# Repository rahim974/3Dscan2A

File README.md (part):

# 3Dscan2A : prototype A (carte fille sur STM32N6570-DK)

Scanner 3D portable, projet ENSEA 2A. Cette branche (`prototype_A`) porte le **prototype A** : une carte fille enfichée sur le kit ST **STM32N6570-DK**, comme un shield Arduino. Le kit apporte le calcul (STM32N6 avec NPU), la caméra IMX335 et l'écran. La carte fille apporte les capteurs et le sans-fil.

Le prototype C (carte autonome STM32H7S3, LQFP-144) viendra ensuite et réutilisera les blocs lidar, IMU et Wi-Fi validés ici.

```
            ┌──────────────────────── Carte fille (ce PCB) ────────────────────────┐
            │  VL53L9CX ◄─ I3C 1,8 V ─ TCA39306 ─ I3C 3,3 V ┐                      │
            │  LSM6DSV16X ◄──────────── I²C 3,3 V ──────────┤                      │
            │  ST67W611M1 ◄──────────── SPI 3,3 V ──────────┤   connecteurs        │
            │  LDO 3V3 / 1V8 / 1V2, oscillateur 24 MHz      ├── Arduino            │
            └───────────────────────────────────────────────┼──────────────────────┘
                                                            ▼
                      STM32N6570-DK : STM32N6 + NPU, caméra IMX335, écran, USB
                                                            │ Wi-Fi 6 / USB
                                                            ▼
                                                 PC : reconstruction 3D
```

**Répartition du traitement** (décidée le 03/11/2026) :

- **Sur le kit** : l'IA tourne sur le NPU et détecte ou segmente les objets sur l'image caméra. Elle fusionne le résultat avec la profondeur du lidar et l'orientation de l'IMU. L'**écran du kit** affiche en direct l'image, la profondeur et les objets détectés : c'est le retour visuel pendant le scan.
- **Sur le PC** : il reçoit les données déjà traitées par **Wi-Fi** (profondeur + étiquettes + orientation, horodatées) et assemble le **modèle 3D complet de la pièce** (recalage des nuages de points, maillage). Le N6 n'a ni la mémoire ni la puissance pour cette étape.
- L'USB du kit reste une solution de repli filaire pour envoyer les mêmes données.

---

## 1. Le PCB KiCad à concevoir

Une carte 2 couches au format shield Arduino Uno R3, sans microcontrôleur, sans BGA et sans mémoire externe. Elle s'enfiche sur les 4 barrettes Arduino du kit (CN8, CN7, CN11, CN12).

**État (08/11/2026)** : le projet KiCad est dans [`carte_fille_A/`](carte_fille_A/). Il part du schéma du prototype 1 (mêmes symboles et empreintes pour le lidar, l'IMU et le Wi-Fi). Le 08/11/2026, tous les composants actifs et connecteurs ont été revus avec leurs datasheets ; les corrections sont listées dans « Points à vérifier » ci-dessous.

- **Schéma** : 6 feuilles, ERC sans erreur. Un seul avertissement, exclu volontairement : la bille E5 (VSS) du lidar passe par R14 avant la masse.
- **PCB** : contour Uno R3 (68,6 × 53,3 mm), les 4 barrettes en place côté B, empreintes pré-placées par bloc, plan de masse sur B.Cu. Mis à jour depuis le schéma le 08/11/2026 (TCA39306 en VSSOP-8, R11 à R14, C36, J5 en 1×5) : placer les nouvelles empreintes. **Pas encore routé.**
- Le schéma et le placement sont générés par `carte_fille_A/generateur/design_A.py` puis `pcb_A.py` (Python de KiCad). Une fois qu'on retouche à la main dans KiCad, on ne relance plus les scripts.

| Feuille | Contenu |
|---|---|
| `connecteurs` | 4 barrettes Arduino mâles (CN8, CN7, CN11, CN12), point de test IOREF |
| `alimentation` | 5 V du kit → LD39150 (+3V3) → LDK130 (+1V8, +1V2), LED de présence, points de test |
| `lidar` | VL53L9CX, translateur I3C TCA39306, 3 × SN74LVC1T45 (XSHUT, SYNC_IN, INTR), oscillateur 24 MHz |
| `imu` | LSM6DSV16X sur le bus D14/D15, INT1/INT2 |
| `wifi` | ST67W611M1 sur le SPI5 (D10–D13), SPI_RDY, CHIP_EN, UART vers D0/D1 et header UART/BOOT |
| `mecanique` | 2 trous M2 pour le module caméra |

**Affectation des broches Arduino**

| Broche | Port N6 | Signal |
|---|---|---|
| D0 / D1 | PF6 / PD5 | UART du module Wi-Fi (par 0 Ω) |
| D2 | PD0 | Wi-Fi SPI_RDY (EXTI) |
| D3 | PE9 | SYNC_IN du lidar (sortie timer, TIM1_CH1 à confirmer) |
| D4 | PH5 | INTR du lidar (EXTI) |
| D5 | PE10 | INT1 de l'IMU (EXTI 10) |
| D7 | PD6 | CHIP_EN du Wi-Fi |
| D8 | PE7 | XSHUT du lidar |
| D9 | PE14 | INT2 de l'IMU (EXTI 14). Pas D6/PE13 : l'EXTI 13 sert au bouton USER1 du kit (PC13). |
| D10–D13 | PA3, PG2, PH8, PE15 | SPI5 vers le Wi-Fi (NSS, MOSI, MISO, SCK) |
| D14 / D15 | PC1 / PH9 | Bus I3C du lidar et de l'IMU (I3C vérifié dans CubeMX le 03/11/2026) |
| CN8 5V / GND | | Alimentation de la carte |

**Points à vérifier avant le routage**

- ~~**I3C sur D14/D15**~~ : vérifié dans CubeMX. Reste à voir **quels composants du kit sont déjà sur I2C1 (PH9/PC1)** : un composant I²C sans filtre anti-parasites de 50 ns peut perturber l'I3C. Les options de repli (I3C sur A4/A5, pull-ups I²C) ont été retirées de la carte le 03/11/2026 : en cas de problème, il faudra une nouvelle version du PCB.
- **Timer sur PE9** (D3) pour SYNC_IN : vérifier dans CubeMX qu'une sortie timer y est disponible (TIM1_CH1 ?).
- **EXTI** : D2 = ligne 0, D4 = ligne 5, D5 = ligne 10, D9 = ligne 14. Ne pas activer en interruption le TOF_INT de la caméra (PQ0, ligne 0), qui est en conflit avec D2.
- **Translateur I3C** : le NXP P3A9606 prévu au départ est limité à 1,98 V des deux côtés, donc incompatible avec le 3,3 V du kit. Il est remplacé par le **TI TCA39306DCUR** (VSSOP-8), câblé selon la figure 9-7 du datasheet : 200 kΩ + 100 pF sur VREF2/EN, pull-ups 2,2 kΩ côté 1,8 V (et non 1 kΩ : le lidar ne garantit son niveau bas qu'à faible courant, et le kit ajoute déjà 1,5 kΩ côté 3,3 V). C'est un FET passif : démarrer l'I3C en push-pull vers 5 MHz et monter en vérifiant les fronts (ST annonce 30 images/s en 54 × 42 sur I3C).
- **Revue datasheets du 08/11/2026** (autres corrections) :
  - Condensateur de découplage de l'oscillateur Y1 (C12) déplacé du +3V3 au **+1V8**, la tension d'alimentation de Y1.
  - Bille **E5** du lidar reliée à la masse par **R14 (0 Ω)** : VSS dans la datasheet rev 9, mais nommée VPP sur les cartes d'évaluation ST. On retire R14 si ST confirme que c'est VPP.
  - **J5** passe en 1×5 (GND, TX, RX, BOOT, +3V3) : un cavalier entre les broches 4 et 5 met BOOT à 1 pour la mise à jour du module Wi-Fi.
  - **LDO 3,3 V** : le rail peut tirer environ 1 A en pointe (lidar + Wi-Fi). On garde le LD39150 avec une grande zone de cuivre et des vias sous sa languette ; on passera à un régulateur à découpage si la consommation moyenne mesurée dépasse environ 0,6 A.
- **Sens de la carte** : en vue de dessus, CN8/CN7 sont en bas et D15…D0 en haut, comme une Uno vue de dessus et comme sur la photo du dessous du kit. L'empreinte KiCad `Module:Arduino_UNO_R3` met l'alimentation en haut, ce qui donnerait une carte en miroir : je ne l'ai pas utilisée. À contrôler en posant un tirage papier 1:1 sur le kit.
- ~~**Antenne Wi-Fi**~~ : au bord côté CN7, tournée vers l'extérieur, avec une zone sans cuivre sur toutes les couches (12,3 × 4,9 mm, DS14784 §6.2). ST conseille de mettre le module dans un coin de la carte, ce qui n'est pas possible ici à cause des barrettes. On le garde au milieu du bord.
- ~~**Empreintes ST**~~ (vérifiées le 03/11/2026, elles viennent d'Ultra Librarian et SnapEDA, pas de ST) :
  - VL53L9CX : 42 pastilles conformes au « solder pattern » du datasheet (DS14879, figure 30).
  - ST67W611M1 : 36 pastilles conformes à la figure 8 de DS14784, brochage conforme au tableau 1.
  - LSM6DSV16X : 14 pastilles qui couvrent les plots du boîtier (DS13510, figure 33), sens du boîtier correct. J'ai corrigé son courtyard, qui était mal formé.
- **Trous de la caméra** (H1, H2) au bord opposé, côté nappe, à côté du lidar : entraxe à mesurer sur le module.

**Orientation retenue (d'après les photos du kit)**

Les connecteurs Arduino (CN8 alimentation, CN7 A0–A5, D0–D15) sont **sous le kit**, sur la face opposée à l'écran. Le STMod+ (CN4) est sur la face de l'écran, au bord haut. La caméra n'est pas soudée au kit : c'est un module séparé relié par une **nappe** au bord haut.

On tient donc le scanner comme un appareil photo, écran vers l'utilisateur :

```
   utilisateur  →  [ écran ]  kit MB1939  [ carte fille ]  →  lidar + caméra  →  scène
                                  (Arduino dessous)
```

- La carte fille s'enfiche **sous le kit**, et le lidar est sur sa face extérieure. Il regarde la scène, à l'opposé de l'écran : c'est le bon sens.
- Le **module caméra est fixé sur la carte fille**, à côté du lidar, avec des entretoises. La nappe fait le tour du bord haut du kit. Le lidar et la caméra sont alors rigidement liés et regardent dans la même direction, ce qui simplifie l'étalonnage.
- Le **STMod+ n'est pas utilisé** : il est sur l'autre face du kit, il faudrait une nappe pour le rejoindre, et il n'apporte rien que l'Arduino n'ait déjà (son SPI5 est le même que sur D10–D13, son UART le même que sur D0/D1). On ne le garde qu'en **repli** : si l'I3C du N6 ne sort pas sur l'Arduino mais sur une broche du STMod+, on le relie par un petit câble plat.

**Contraintes de placement**

- Le lidar doit regarder **dans la même direction que la caméra**. Avec l'orientation ci-dessus, la carte fille doit prévoir les trous de fixation du module caméra à côté du lidar.
- La carte fille doit éviter les composants hauts du dessous du kit : prise Ethernet, USB-A, jack audio, lecteur micro-SD, et laisser l'accès aux USB-C (ST-LINK et USB1). Les entretoises du kit (pieds en laiton aux coins) donnent la hauteur minimale.
- L'**antenne PCB** du module Wi-Fi doit être en bord de carte, sans cuivre ni composant dessous ni autour (voir le datasheet du module), et loin des parties métalliques du kit.
- L'IMU près du lidar, sur la même carte rigide, pour que la transformation lidar ↔ IMU reste fixe.
- Les pistes I3C courtes et sans stub, le translateur au plus près du lidar.

---

## 2. Composants nécessaires

### Actifs

| Composant | Référence | Boîtier | Utilité |
|---|---|---|---|
| Lidar 3D ToF | ST **VL53L9CX** (commande : VL53L9CXV0VE/1) | Module LGA | Carte de profondeur 54×42 zones, jusqu'à 8,8 m |
| Centrale inertielle 6 axes | ST **LSM6DSV16X** | LGA-14 | Orientation et mouvement du scanner (fusion SFLP) |
| Module Wi-Fi 6 / BLE 5.4 | ST **ST67W611M1** | Module LGA, antenne PCB | Envoi des scans au PC, commandes en BLE |
| Translateur I3C 3,3 V ↔ 1,8 V | TI **TCA39306DCUR** | VSSOP-8 | Passe l'I3C du N6 (3,3 V) au lidar (1,8 V), jusqu'à 12,5 MHz |
| Translateur GPIO 3,3 V ↔ 1,8 V | TI **SN74LVC1T45** ×3 | SOT-23-6 | XSHUT, INTR et SYNC_IN du lidar |
| Oscillateur 24 MHz 1,8 V | ECS-2520MV-240 (1,6 à 3,6 V) | 2520 | Horloge AP_CLK du lidar |
| LDO 1,8 V 300 mA | ST **LDK130-18** | SOT-23-5 | IOVDD du lidar, côté 1,8 V des translateurs, oscillateur |
| LDO 1,2 V 300 mA | ST **LDK130-12** | SOT-23-5 | DVDD du lidar |
| LDO 3,3 V 1,5 A | ST **LD39150DT33** | DPAK | 3V3 depuis le 5 V du kit pour le Wi-Fi et le lidar (pointes ≈ 1 A) |

### Passifs et connectique

| Composant | Utilité |
|---|---|
| Barrettes mâles Arduino Uno R3 : 1×10, 1×8, 1×8, 1×6, pas de 2,54 mm (hauteur à choisir selon §3) | Enfichage sur le kit |
| Header 1×5, 2,54 mm | UART + BOOT + 3,3 V du module Wi-Fi (cavalier BOOT) |
| Condensateurs 100 pF / 100 nF / 1 µF (0402), 4,7 µF / 10 µF (0603), 22 µF (0805) | Découplage du lidar, du Wi-Fi, de l'IMU et des LDO |
| Résistances 1 kΩ, 2,2 kΩ, 10 kΩ, 100 kΩ, 200 kΩ, 33 Ω, 0 Ω | Pull-ups et pull-downs (I3C, XSHUT, SYNC, INTR, CHIP_EN, BOOT), polarisation du TCA39306, série de l'horloge, liaison UART Wi-Fi ↔ D0/D1, masse de E5 |
| LED + résistance | Présence d'alimentation |

Les valeurs exactes sont dans [`carte_fille_A/Nomenclature_carte_fille_A.md`](carte_fille_A/Nomenclature_carte_fille_A.md), et les références à commander dans [`carte_fille_A/Achats_composants_specifiques.md`](carte_fille_A/Achats_composants_specifiques.md).

---

## 3. Mesures et vérifications à faire sur le kit

À faire **avant** de dessiner le contour du PCB. Sources : schéma MB1939 (STM32N6570-DK, rév. C-02), user manual UM3300 et le kit lui-même avec un pied à coulisse.

### Mécanique

- [x] **Face des connecteurs** (photos du 03/11/2026) : Arduino CN7/CN8 et D0–D15 **sous le kit**, STMod+ CN4 **côté écran** (bord haut), caméra sur nappe au bord haut.
- [ ] **Position exacte** des barrettes Arduino (cote depuis un coin de la carte, entraxe) au pied à coulisse.
- [ ] **Module caméra** (MB1854 / B-CAMS-IMX) : dimensions, entraxe de ses trous de fixation, côté de l'objectif, longueur de la nappe (vérifiée le 03/11/2026 : assez longue pour faire le tour du bord haut jusqu'à la carte fille).
- [ ] **Hauteur sous le kit** : hauteur des entretoises en laiton et des composants les plus hauts (Ethernet, USB-A, jack audio). En déduire la hauteur des barrettes (empilables ou rallongées) et la zone libre pour la carte fille.
- [ ] Accès aux USB-C ST-LINK et USB1 et au lecteur micro-SD une fois la carte fille montée.
- [ ] Le module caméra semble porter son propre capteur ToF et une IMU (lignes TOF_INT / IMU_INT du connecteur) : identifier les références sur la carte.

### Électrique

- [ ] **Tension des I/O** sur les connecteurs Arduino et STMod+ (VDDIO à 3,3 V ou 1,8 V ? réglable ?). Si les I/O sont déjà en 1,8 V, on retire les translateurs.
- [ ] **Courant disponible** sur la broche 5V de l'Arduino : l'UM3300 ne donne pas de maximum pour cette broche. Par l'USB ST-LINK (CN6), le kit peut être limité à 550 mA ; par l'USB-C CN18 (JP2 sur USB_SNK), il accepte jusqu'à 3 A. **Alimenter le kit par CN18** et mesurer la consommation de la carte fille (LD39150 sur le 5 V, pointes ≈ 1 A).
- [ ] **Alimentation portable** : power bank USB-C 5 V / 3 A sur un port USB-C du kit, sans PC. Vérifier dans l'UM3300 (« Power supply ») la position du cavalier de source et le courant maximal de chaque port. Mesurer la consommation réelle du kit + carte fille (estimée à 1,5–2 A).
- [ ] Plus tard : alimenter le kit par la broche VIN de CN8 depuis une batterie sur la carte fille ?
- [ ] **Pull-ups 1,5 kΩ** de l'I2C1 (PH9/PC1, R153/R149 vers VDDIO) : vérifier si elles gênent l'I3C et s'il faut retirer R153/R149.

### Broches (avec STM32CubeMX sur le STM32N657X0H3)

Relevé du schéma MB1939 page 3 :

| Connecteur | Broches | Port du N6 |
|---|---|---|
| Arduino D0–D7 | D0 PF6, D1 PD5, D2 PD0, D3 PE9, D4 PH5 (ou PC13 par SB44), D5 PE10, D6 PE13, D7 PD6 | |
| Arduino D8–D13 | D8 PE7, D9 PE14, **D10 PA3, D11 PG2, D12 PH8, D13 PE15** | D10–D13 = **SPI5** (NSS, MOSI, MISO, SCK) |
| Arduino A0–A5 | A0 PA5, A1 PA9, A2 PA10, A3 PA12, A4 PF3, A5 PB10 | |
| I2C1 | SCL PH9, SDA PC1 | pull-ups 1,5 kΩ, a priori sur D15/D14 de l'Arduino *(à confirmer)* |
| I2C2 | SCL PD14, SDA PD4 | pull-ups 1,5 kΩ |
| STMod+ SPI5 | NSS PA3, MOSI PG2, MISO PH8, SCK PE15 | **partagé** avec D10–D13 |
| STMod+ divers | UART TX PD5 / RX PF6 / CTS PG5 / RTS PG14, INT PC11, RST PB3, PWM PC7, ADC PC9, IO1–IO4 PD13 / PF1 / PB8 / PG9 | TX/RX partagés avec D0/D1 |

À vérifier :

- [ ] **I3C** : quelles broches I3C1/I3C2 du N6 tombent sur l'Arduino ou le STMod+ (PH9/PC1 ? PD14/PD4 ?). C'est le point bloquant du prototype A.
- [ ] **SPI5** sur D10–D13 pour le Wi-Fi, et une broche libre pour SPI_RDY (interruption EXTI) et une pour CHIP_EN.
- [ ] Une sortie **timer** libre pour SYNC_IN du lidar, et des EXTI pour INTR du lidar et INT1/INT2 de l'IMU.
- [ ] Conflits avec les fonctions du kit déjà câblées sur ces broches (Ethernet, LCD, audio, SD, USB…).
- [ ] Le connecteur caméra porte déjà **TOF_INT / TOF_LPn (PQ0/PQ5) et IMU_INT1/2 (PQ1/PQ2)** : vérifier ce que le module caméra embarque (ToF et IMU ?) et si on peut s'en servir pour les premiers tests.

---

## 4. Étapes suivantes

1. **Relevés sur le kit** (§3) : cotes mécaniques, tension des I/O, courant disponible, broches I3C/SPI. Les noter dans `docs/kit_mesures.md`.
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
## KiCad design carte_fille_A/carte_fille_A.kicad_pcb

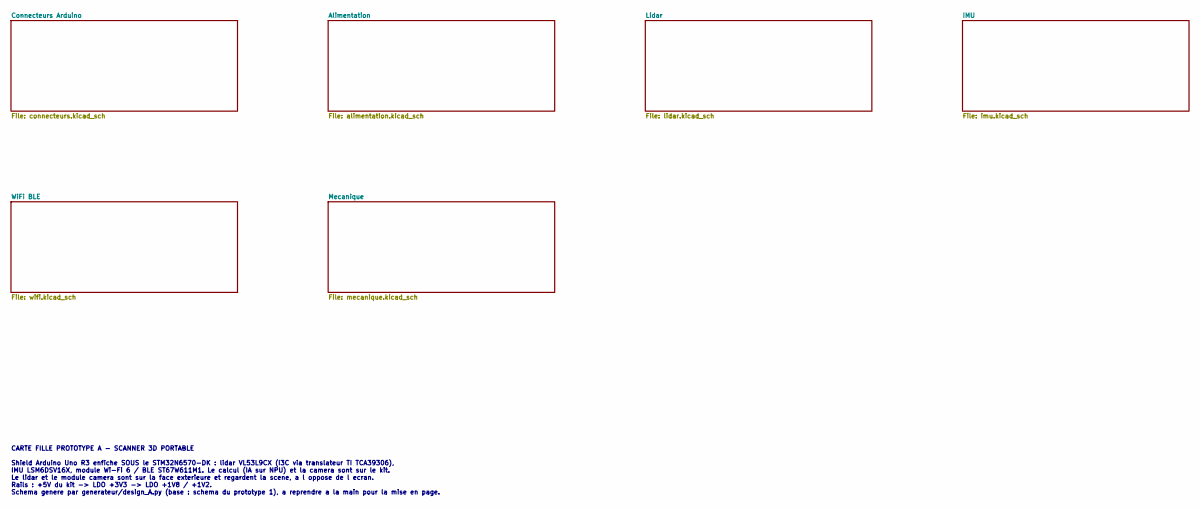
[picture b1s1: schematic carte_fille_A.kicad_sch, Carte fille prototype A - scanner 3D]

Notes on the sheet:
CARTE FILLE PROTOTYPE A - SCANNER 3D PORTABLE Shield Arduino Uno R3 enfiche SOUS le STM32N6570-DK : lidar VL53L9CX (I3C via translateur TI TCA39306), IMU LSM6DSV16X, module Wi-Fi 6 / BLE ST67W611M1. Le calcul (IA sur NPU) et la camera sont sur le kit. Le lidar et le module camera sont sur la face e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

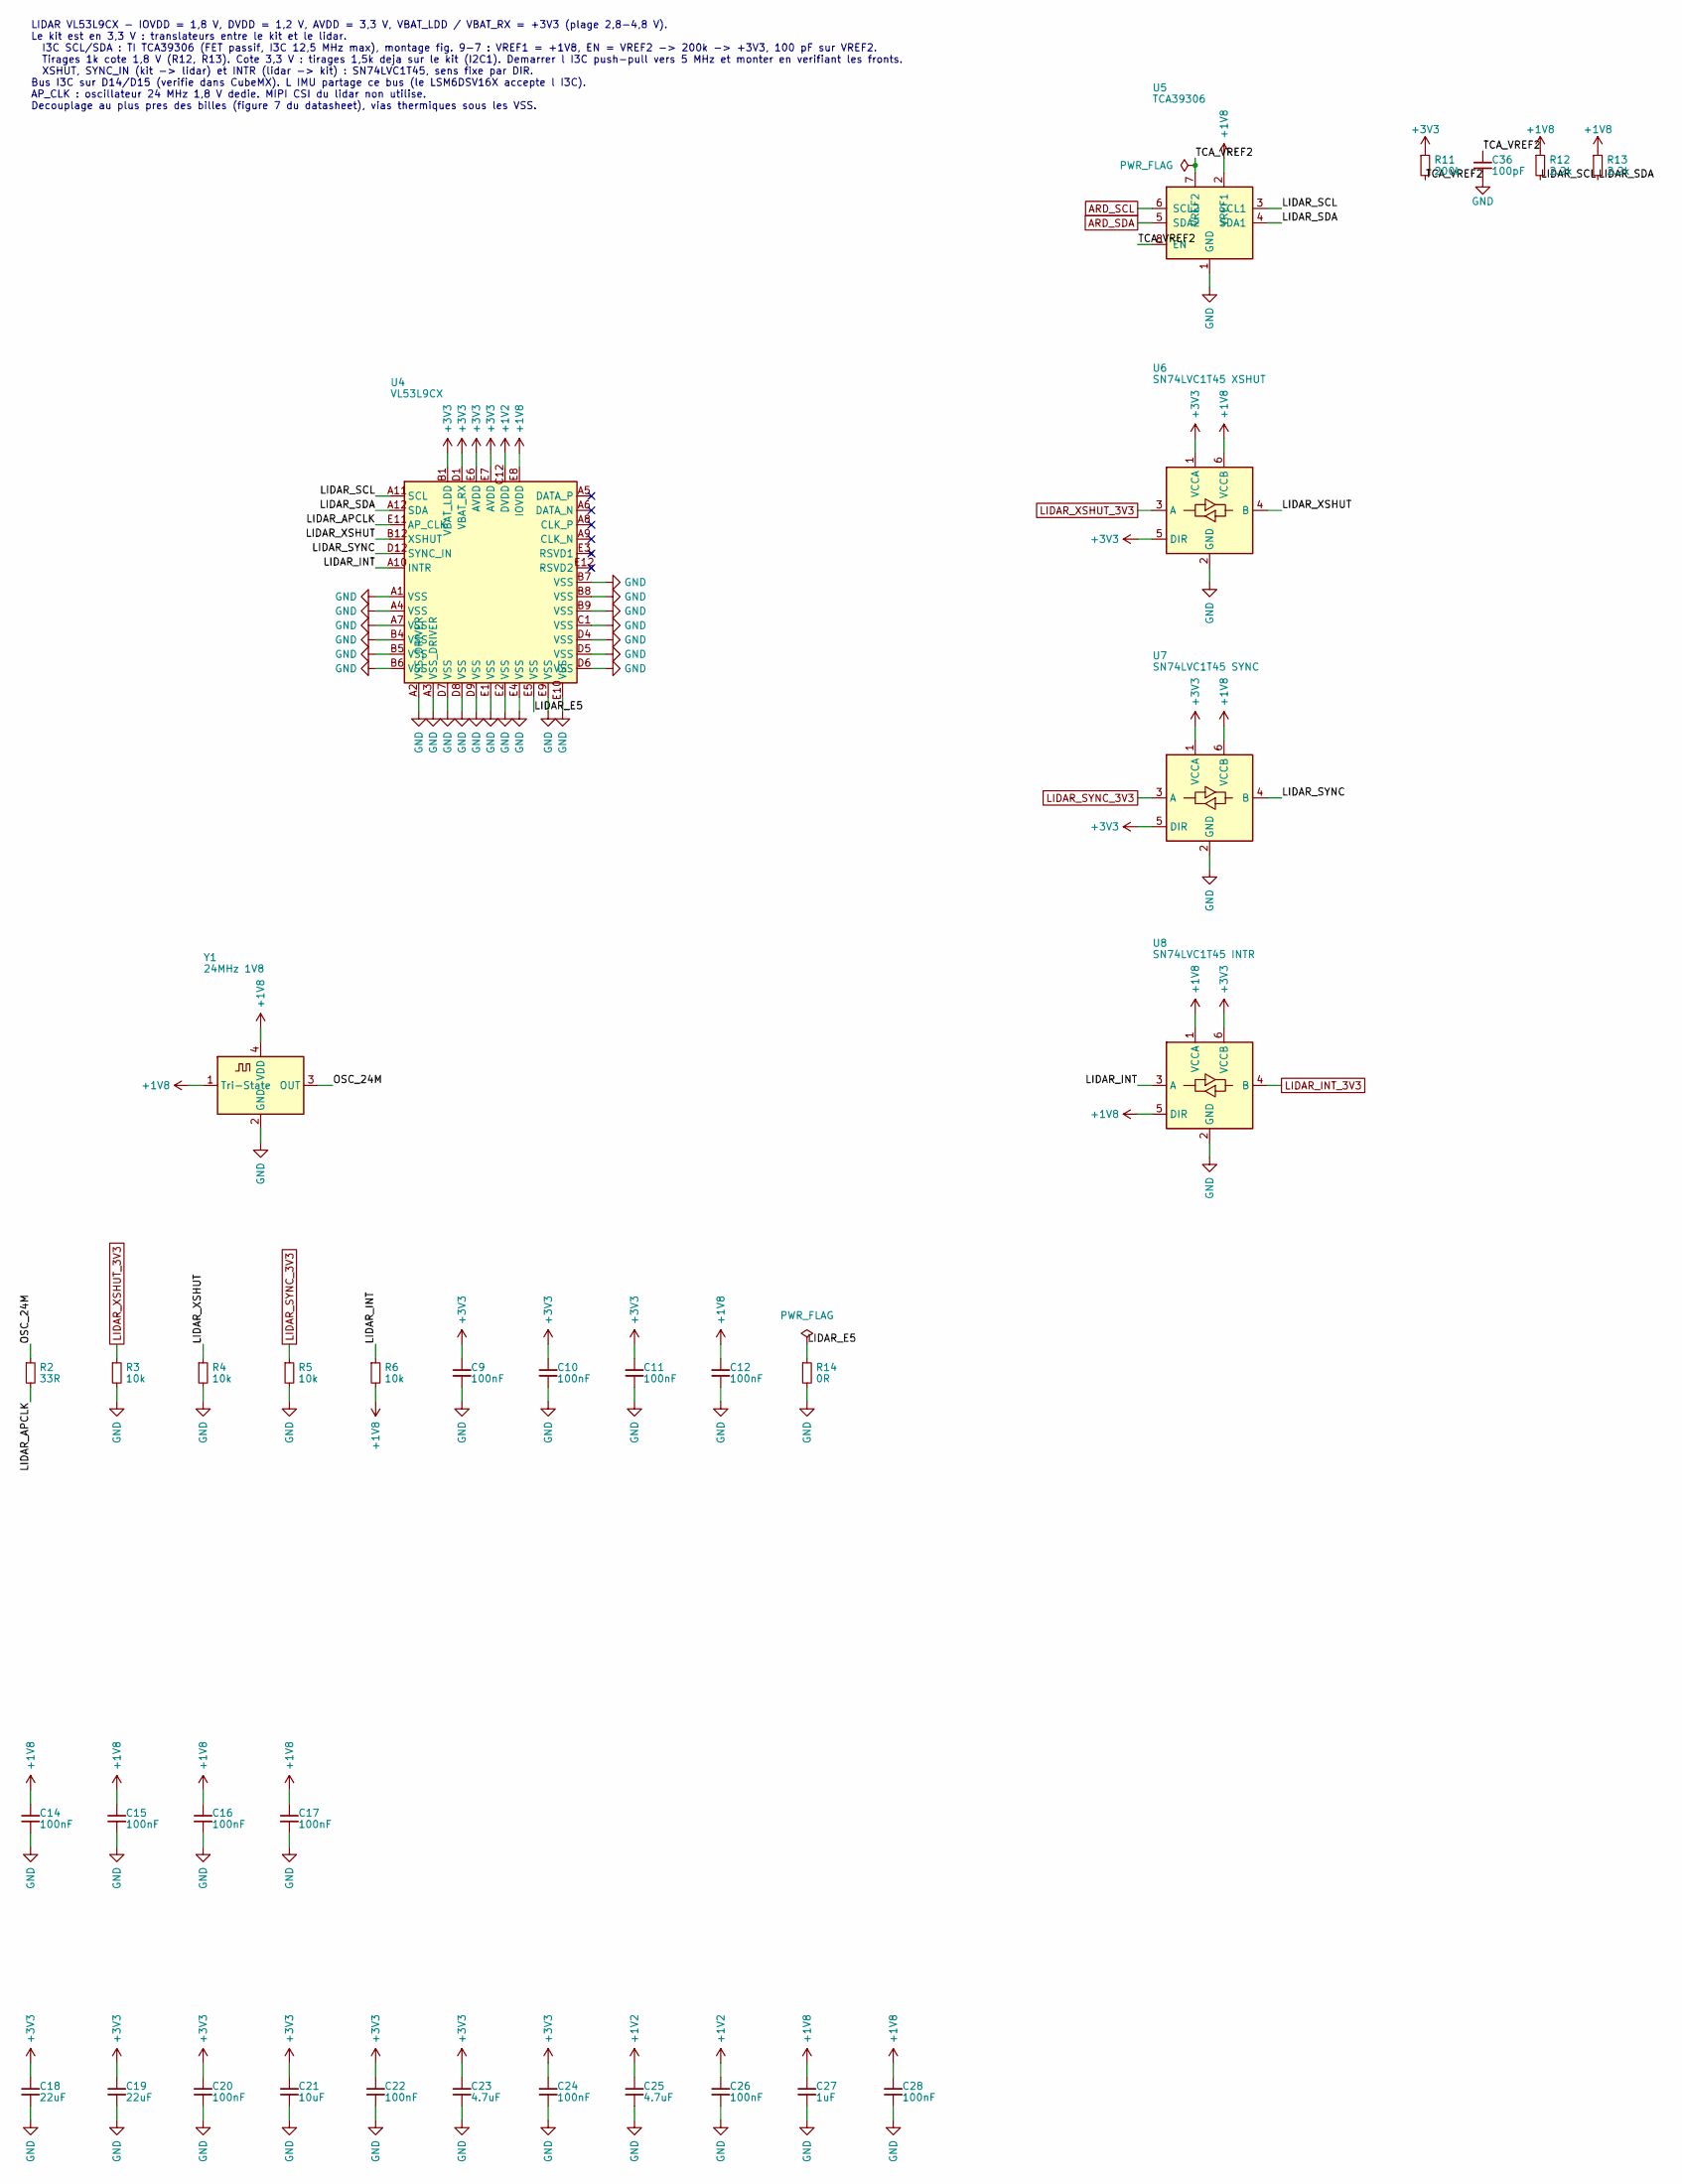
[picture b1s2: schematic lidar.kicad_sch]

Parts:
C9, C10, C11, C12, C14, C15, C16, C17, C20, C22, C24, C26, C28: 100nF; C_0402_1005Metric
C18, C19: 22uF; C_0805_2012Metric
C21: 10uF; C_0603_1608Metric
C23, C25: 4.7uF; C_0603_1608Metric
C27: 1uF; C_0402_1005Metric
C36: 100pF; C_0402_1005Metric
R2: 33R; R_0402_1005Metric
R3, R4, R5, R6: 10k; R_0402_1005Metric
R11: 200k; R_0402_1005Metric
R12, R13: 2.2k; R_0402_1005Metric
R14: 0R; R_0402_1005Metric
U4: VL53L9CX
U5: TCA39306; VSSOP-8_2.3x2mm_P0.5mm
U6: SN74LVC1T45 XSHUT; SOT-23-6
U7: SN74LVC1T45 SYNC; SOT-23-6
U8: SN74LVC1T45 INTR; SOT-23-6
Y1: 24MHz 1V8; Oscillator_SMD_ECS_2520MV-xxx-xx-4Pin_2.5x2.0mm

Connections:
+1V2: C25.1, C26.1, U4.C12 (DVDD); also elsewhere on the board
+1V8: C12.1, C14.1, C15.1, C16.1, C17.1, C27.1, C28.1, R6.2, R12.1, R13.1, U4.E8 (IOVDD), U5.2 (VREF1), U6.6 (VCCB), U7.6 (VCCB), U8.1 (VCCA), U8.5 (DIR), Y1.1 (Tri-State), Y1.4 (VDD); also elsewhere on the board
+3V3: C9.1, C10.1, C11.1, C18.1, C19.1, C20.1, C21.1, C22.1, C23.1, C24.1, R11.1, U4.B1 (VBAT_LDD), U4.D1 (VBAT_RX), U4.E6 (AVDD), U4.E7 (AVDD), U6.1 (VCCA), U6.5 (DIR), U7.1 (VCCA), U7.5 (DIR), U8.6 (VCCB); also elsewhere on the board
/Lidar/LIDAR_APCLK: R2.2, U4.E11 (AP_CLK)
/Lidar/LIDAR_E5: R14.1, U4.E5 (VSS)
/Lidar/LIDAR_INT: R6.1, U4.A10 (INTR), U8.3 (A)
/Lidar/LIDAR_SCL: R12.2, U4.A11 (SCL), U5.3 (SCL1)
/Lidar/LIDAR_SDA: R13.2, U4.A12 (SDA), U5.4 (SDA1)
/Lidar/LIDAR_SYNC: U4.D12 (SYNC_IN), U7.4 (B)
/Lidar/LIDAR_XSHUT: R4.1, U4.B12 (XSHUT), U6.4 (B)
/Lidar/OSC_24M: R2.1, Y1.3 (OUT)
/Lidar/TCA_VREF2: C36.1, R11.2, U5.7 (VREF2), U5.8 (EN)
ARD_SCL: U5.6 (SCL2); also elsewhere on the board
ARD_SDA: U5.5 (SDA2); also elsewhere on the board
GND: C9.2, C10.2, C11.2, C12.2, C14.2, C15.2, C16.2, C17.2, C18.2, C19.2, C20.2, C21.2, C22.2, C23.2, C24.2, C25.2, C26.2, C27.2, C28.2, C36.2, R3.2, R4.2, R5.2, R14.2, U4.A1 (VSS), U4.A2 (VSS_DRIVER), U4.A3 (VSS_DRIVER), U4.A4 (VSS), U4.A7 (VSS), U4.B4 (VSS), U4.B5 (VSS), U4.B6 (VSS), U4.B7 (VSS), U4.B8 (VSS), U4.B9 (VSS), U4.C1 (VSS), U4.D4 (VSS), U4.D5 (VSS), U4.D6 (VSS), U4.D7 (VSS), U4.D8 (VSS), U4.D9 (VSS), U4.E1 (VSS), U4.E2 (VSS), U4.E4 (VSS), U4.E9 (VSS), U4.E10 (VSS), U5.1 (GND), U6.2 (GND), U7.2 (GND), U8.2 (GND), Y1.2 (GND); also elsewhere on the board
LIDAR_INT_3V3: U8.4 (B); also elsewhere on the board
LIDAR_SYNC_3V3: R5.1, U7.3 (A); also elsewhere on the board
LIDAR_XSHUT_3V3: R3.1, U6.3 (A); also elsewhere on the board

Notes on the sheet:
LIDAR VL53L9CX - IOVDD = 1,8 V, DVDD = 1,2 V, AVDD = 3,3 V, VBAT_LDD / VBAT_RX = +3V3 (plage 2,8-4,8 V). Le kit est en 3,3 V : translateurs entre le kit et le lidar. I3C SCL/SDA : TI TCA39306 (FET passif, I3C 12,5 MHz max), montage fig. 9-7 : VREF1 = +1V8, EN = VREF2 -> 200k -> +3V3, 100 pF sur VRE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

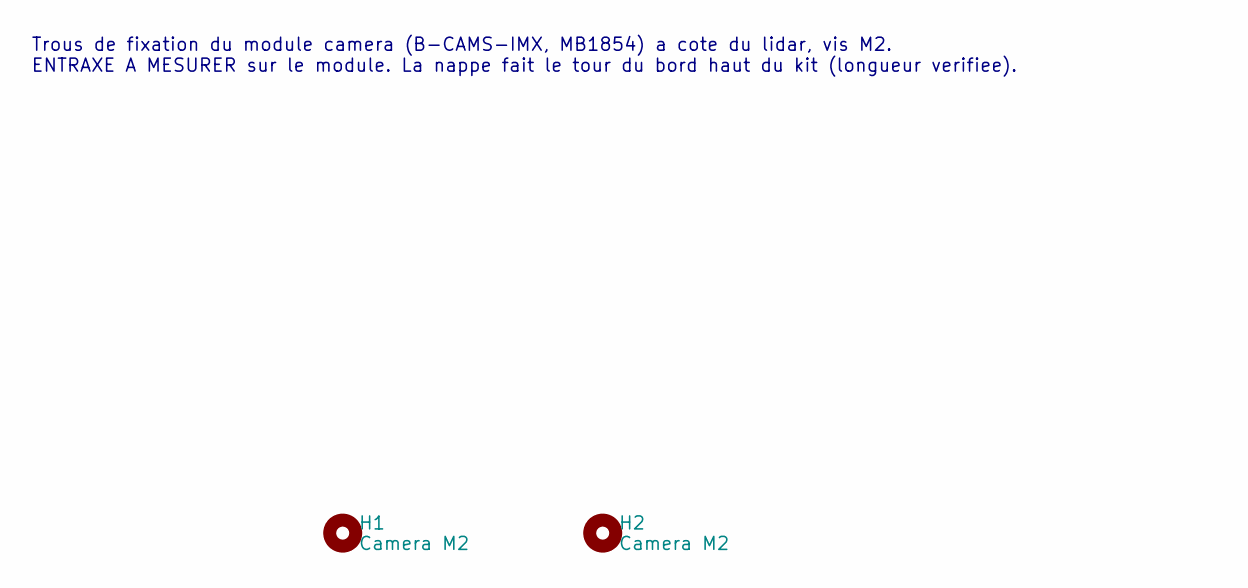
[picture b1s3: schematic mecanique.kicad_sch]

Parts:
H1, H2: Camera M2; MountingHole_2.2mm_M2

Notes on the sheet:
Trous de fixation du module camera (B-CAMS-IMX, MB1854) a cote du lidar, vis M2. ENTRAXE A MESURER sur le module. La nappe fait le tour du bord haut du kit (longueur verifiee).

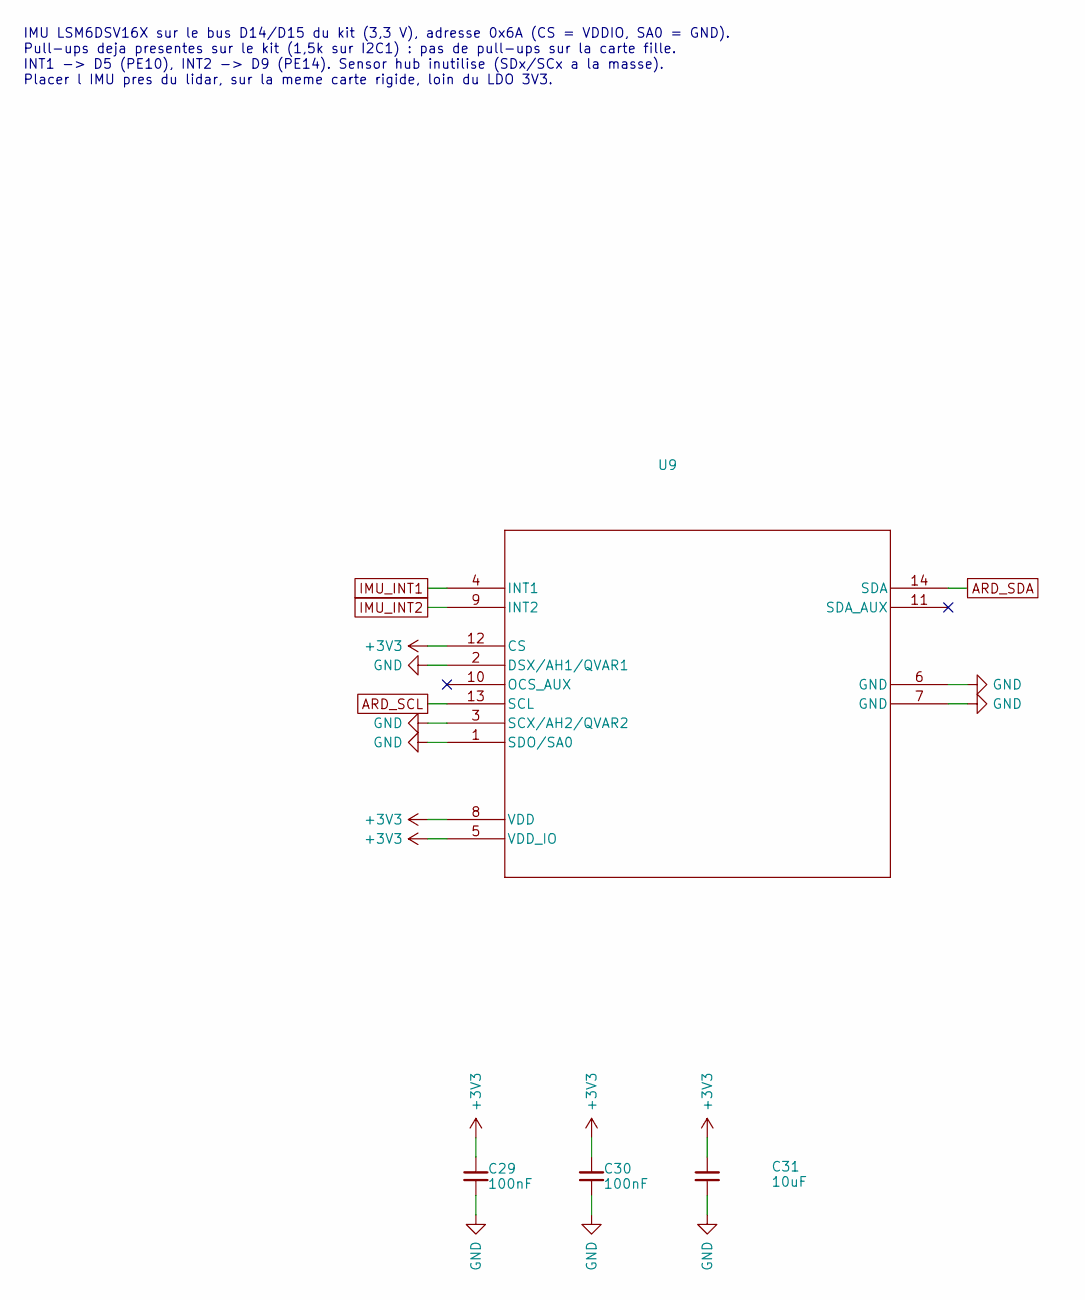
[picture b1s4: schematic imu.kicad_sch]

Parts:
C29, C30: 100nF; C_0402_1005Metric
C31: 10uF; C_0603_1608Metric
U9: LSM6DSV16X; LGA14_LSM6_STM

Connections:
+3V3: C29.1, C30.1, C31.1, U9.5 (VDD_IO), U9.8 (VDD), U9.12 (CS); also elsewhere on the board
ARD_SCL: U9.13 (SCL); also elsewhere on the board
ARD_SDA: U9.14 (SDA); also elsewhere on the board
GND: C29.2, C30.2, C31.2, U9.1 (SDO/SA0), U9.2 (DSX/AH1/QVAR1), U9.3 (SCX/AH2/QVAR2), U9.6 (GND), U9.7 (GND); also elsewhere on the board
IMU_INT1: U9.4 (INT1); also elsewhere on the board
IMU_INT2: U9.9 (INT2); also elsewhere on the board

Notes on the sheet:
IMU LSM6DSV16X sur le bus D14/D15 du kit (3,3 V), adresse 0x6A (CS = VDDIO, SA0 = GND). Pull-ups deja presentes sur le kit (1,5k sur I2C1) : pas de pull-ups sur la carte fille. INT1 -> D5 (PE10), INT2 -> D9 (PE14). Sensor hub inutilise (SDx/SCx a la masse). Placer l IMU pres du lidar, sur la meme c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

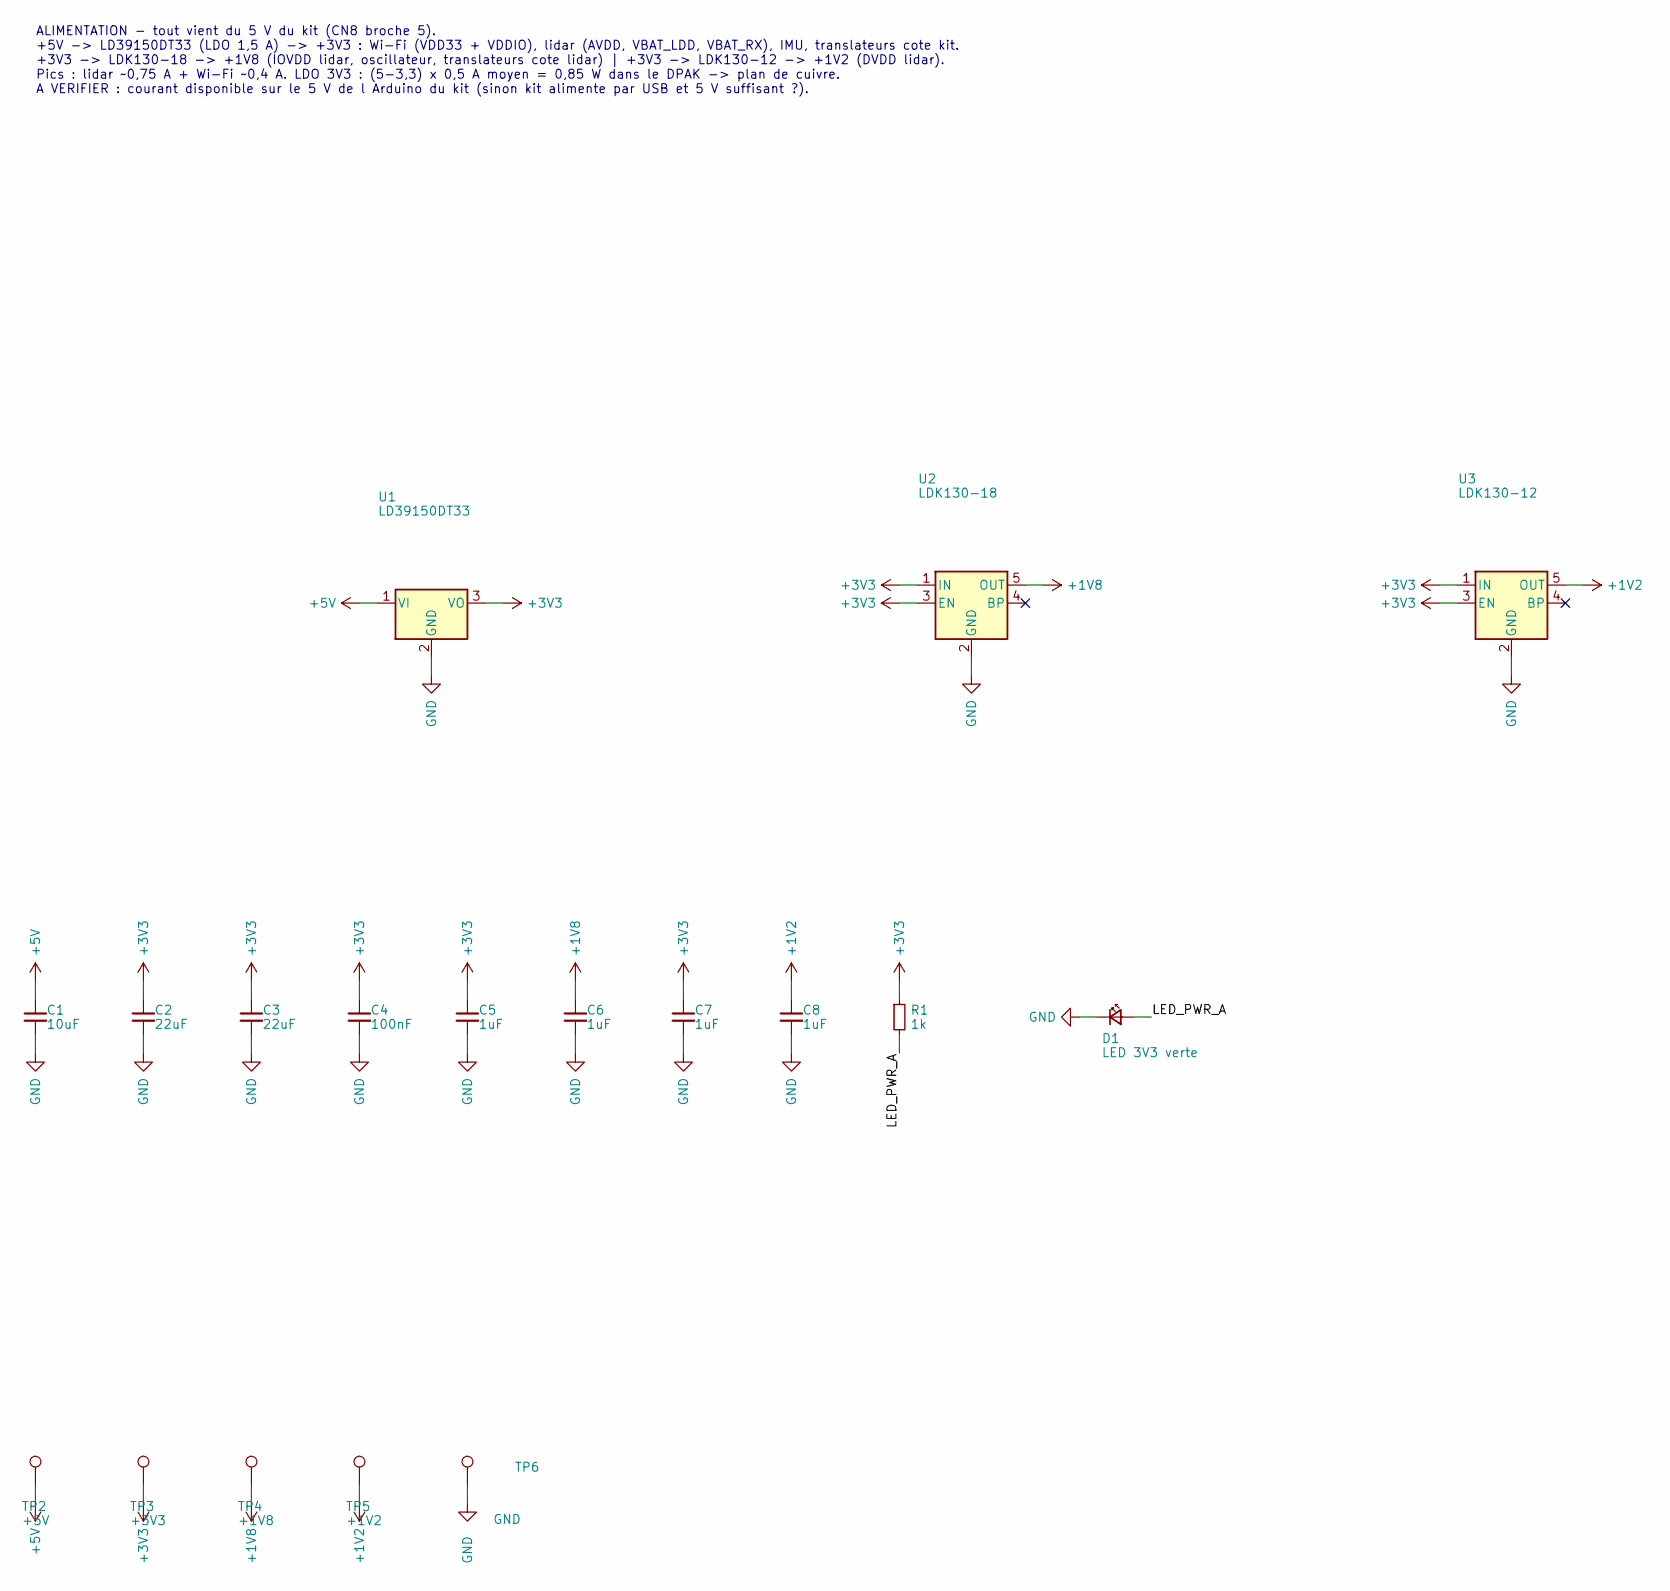
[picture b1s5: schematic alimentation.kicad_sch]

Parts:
C1: 10uF; C_0603_1608Metric
C2, C3: 22uF; C_0805_2012Metric
C4: 100nF; C_0402_1005Metric
C5, C6, C7, C8: 1uF; C_0402_1005Metric
D1: LED 3V3 verte; LED_0603_1608Metric
R1: 1k; R_0402_1005Metric
TP2: +5V; TestPoint_Pad_D1.5mm
TP3: +3V3; TestPoint_Pad_D1.5mm
TP4: +1V8; TestPoint_Pad_D1.5mm
TP5: +1V2; TestPoint_Pad_D1.5mm
TP6: GND; TestPoint_Pad_D1.5mm
U1: LD39150DT33; TO-252-3_TabPin2
U2: LDK130-18; SOT-23-5
U3: LDK130-12; SOT-23-5

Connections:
+1V2: C8.1, TP5.1 (1_1), U3.5 (OUT); also elsewhere on the board
+1V8: C6.1, TP4.1 (1_1), U2.5 (OUT); also elsewhere on the board
+3V3: C2.1, C3.1, C4.1, C5.1, C7.1, R1.1, TP3.1 (1_1), U1.3 (VO), U2.1 (IN), U2.3 (EN), U3.1 (IN), U3.3 (EN); also elsewhere on the board
+5V: C1.1, TP2.1 (1_1), U1.1 (VI); also elsewhere on the board
/Alimentation/LED_PWR_A: D1.2 (A), R1.2
GND: C1.2, C2.2, C3.2, C4.2, C5.2, C6.2, C7.2, C8.2, D1.1 (K), TP6.1 (1_1), U1.2 (GND), U2.2 (GND), U3.2 (GND); also elsewhere on the board

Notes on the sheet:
ALIMENTATION - tout vient du 5 V du kit (CN8 broche 5). +5V -> LD39150DT33 (LDO 1,5 A) -> +3V3 : Wi-Fi (VDD33 + VDDIO), lidar (AVDD, VBAT_LDD, VBAT_RX), IMU, translateurs cote kit. +3V3 -> LDK130-18 -> +1V8 (IOVDD lidar, oscillateur, translateurs cote lidar) | +3V3 -> LDK130-12 -> +1V2 (DVDD lidar)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

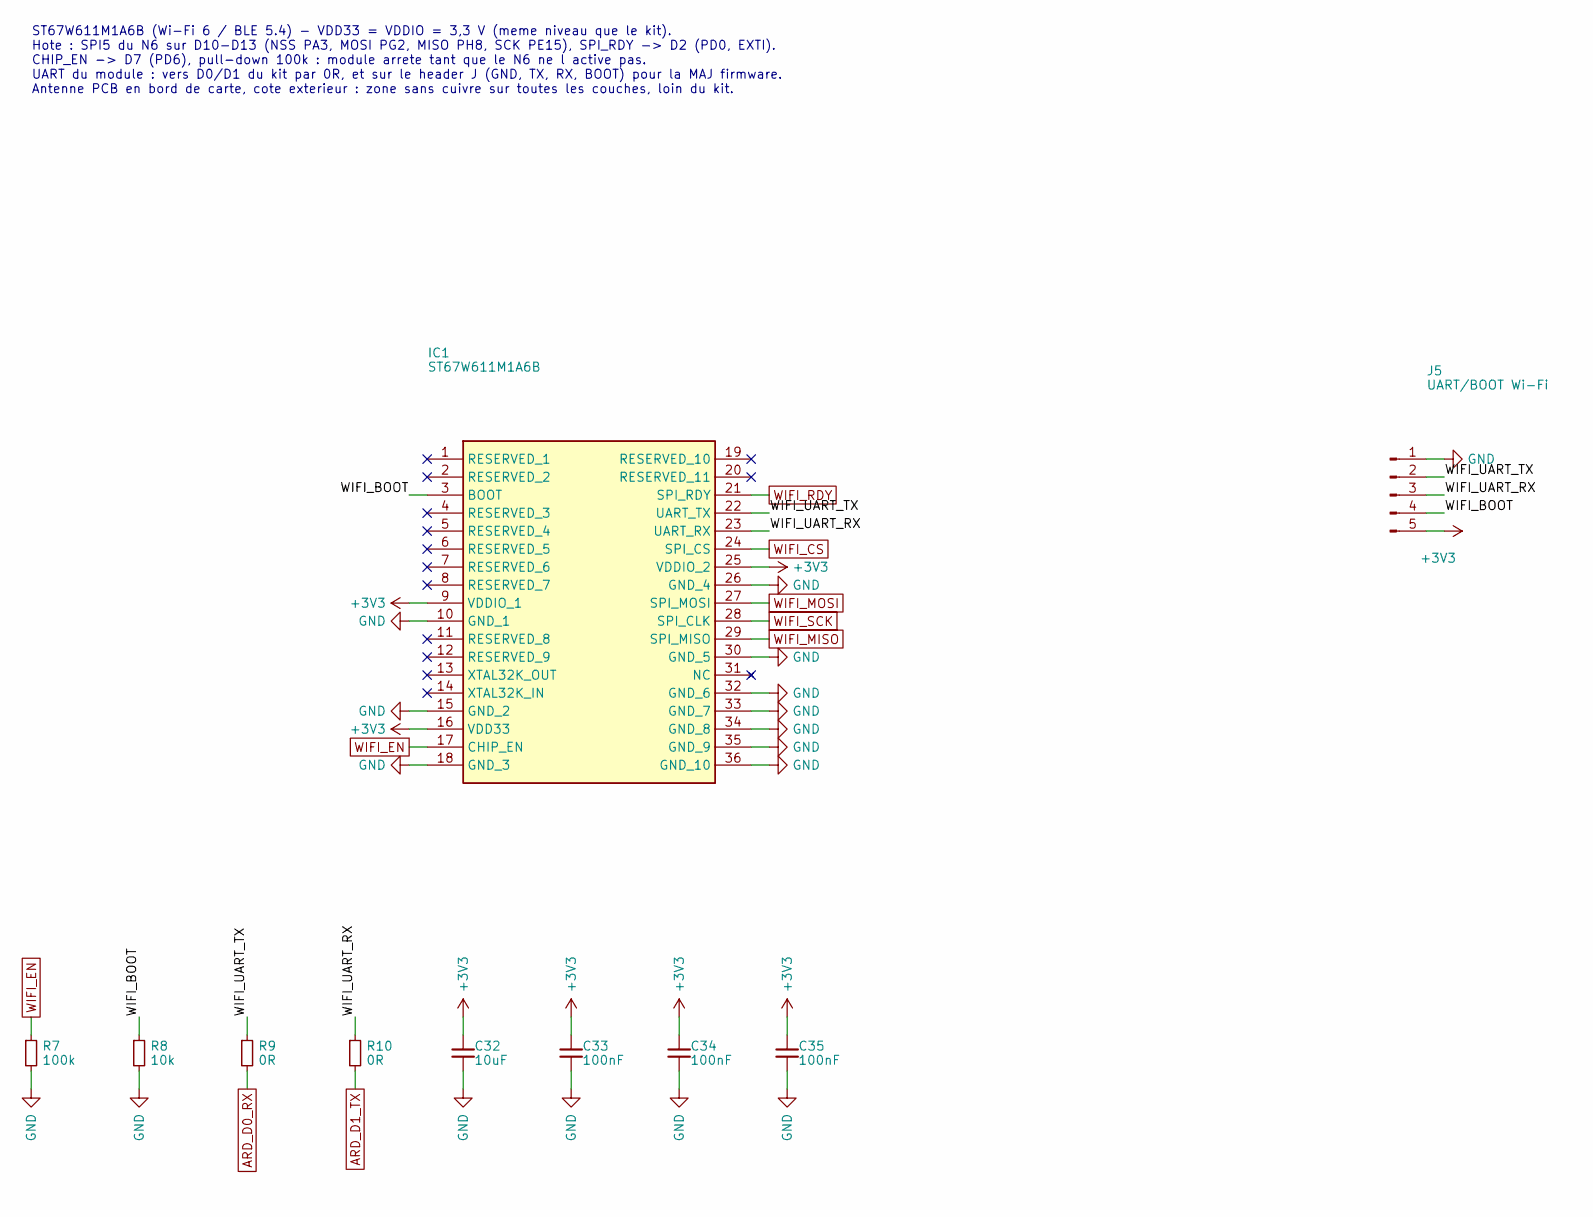
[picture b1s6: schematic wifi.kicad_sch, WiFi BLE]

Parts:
C32: 10uF; C_0603_1608Metric
C33, C34, C35: 100nF; C_0402_1005Metric
IC1: ST67W611M1A6B; Manufacturer_Part_Number ST67W611M1A6B
J5: UART/BOOT Wi-Fi; PinHeader_1x05_P2.54mm_Vertical
R7: 100k; R_0402_1005Metric
R8: 10k; R_0402_1005Metric
R9, R10: 0R; R_0402_1005Metric

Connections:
+3V3: C32.1, C33.1, C34.1, C35.1, IC1.9 (VDDIO_1), IC1.16 (VDD33), IC1.25 (VDDIO_2), J5.5; also elsewhere on the board
/WiFi BLE/WIFI_BOOT: IC1.3 (BOOT), J5.4, R8.1
/WiFi BLE/WIFI_UART_RX: IC1.23 (UART_RX), J5.3, R10.1
/WiFi BLE/WIFI_UART_TX: IC1.22 (UART_TX), J5.2, R9.1
ARD_D0_RX: R9.2; also elsewhere on the board
ARD_D1_TX: R10.2; also elsewhere on the board
GND: C32.2, C33.2, C34.2, C35.2, IC1.10 (GND_1), IC1.15 (GND_2), IC1.18 (GND_3), IC1.26 (GND_4), IC1.30 (GND_5), IC1.32 (GND_6), IC1.33 (GND_7), IC1.34 (GND_8), IC1.35 (GND_9), IC1.36 (GND_10), J5.1, R7.2, R8.2; also elsewhere on the board
WIFI_CS: IC1.24 (SPI_CS); also elsewhere on the board
WIFI_EN: IC1.17 (CHIP_EN), R7.1; also elsewhere on the board
WIFI_MISO: IC1.29 (SPI_MISO); also elsewhere on the board
WIFI_MOSI: IC1.27 (SPI_MOSI); also elsewhere on the board
WIFI_RDY: IC1.21 (SPI_RDY); also elsewhere on the board
WIFI_SCK: IC1.28 (SPI_CLK); also elsewhere on the board

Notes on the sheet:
ST67W611M1A6B (Wi-Fi 6 / BLE 5.4) - VDD33 = VDDIO = 3,3 V (meme niveau que le kit). Hote : SPI5 du N6 sur D10-D13 (NSS PA3, MOSI PG2, MISO PH8, SCK PE15), SPI_RDY -> D2 (PD0, EXTI). CHIP_EN -> D7 (PD6), pull-down 100k : module arrete tant que le N6 ne l active pas. UART du module : vers D0/D1 du ki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

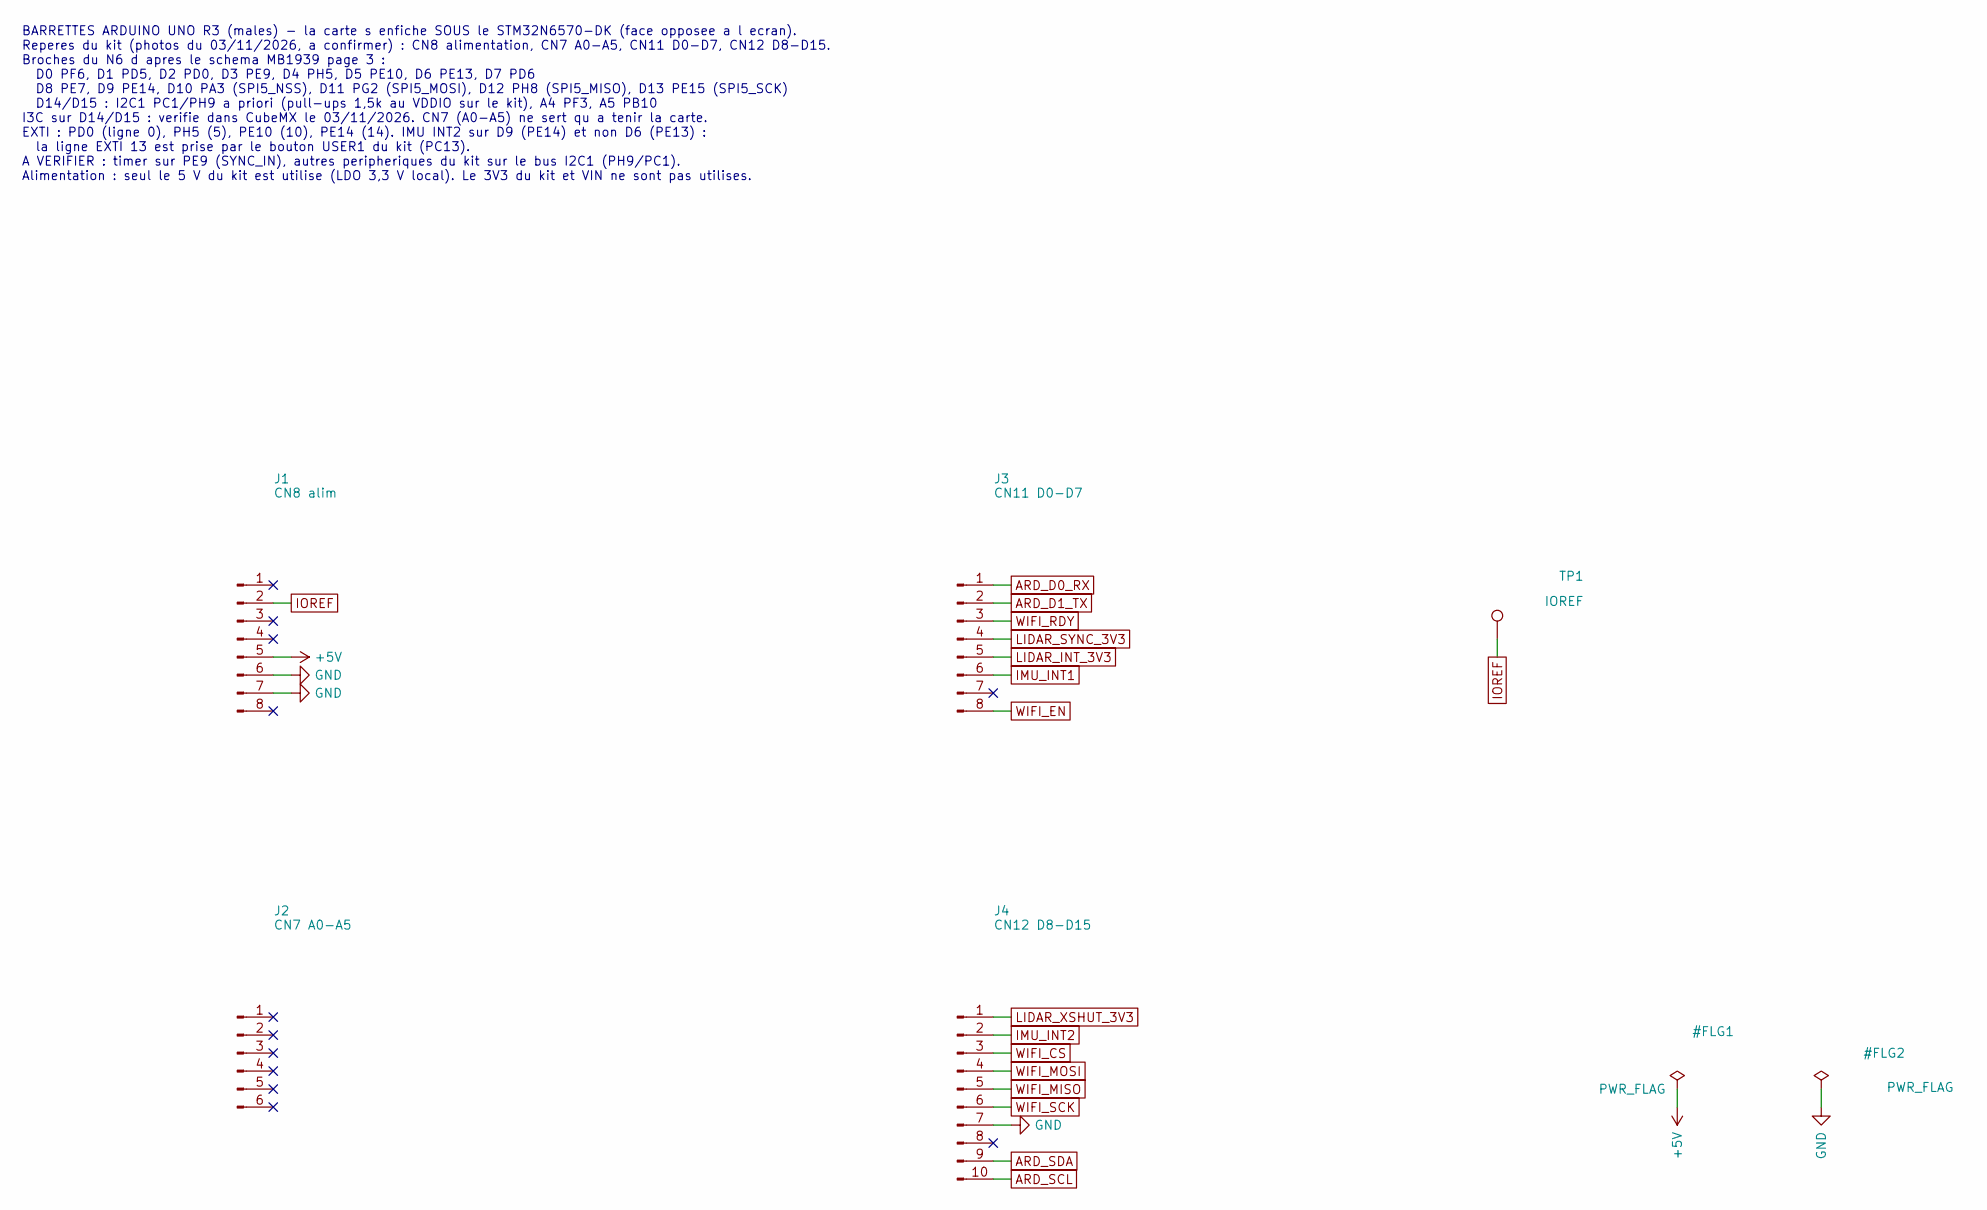
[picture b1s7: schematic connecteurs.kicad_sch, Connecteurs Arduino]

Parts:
J1: CN8 alim; PinHeader_1x08_P2.54mm_Vertical
J2: CN7 A0-A5; PinHeader_1x06_P2.54mm_Vertical
J3: CN11 D0-D7; PinHeader_1x08_P2.54mm_Vertical
J4: CN12 D8-D15; PinHeader_1x10_P2.54mm_Vertical
TP1: IOREF; TestPoint_Pad_D1.5mm

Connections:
+5V: J1.5; also elsewhere on the board
ARD_D0_RX: J3.1; also elsewhere on the board
ARD_D1_TX: J3.2; also elsewhere on the board
ARD_SCL: J4.10; also elsewhere on the board
ARD_SDA: J4.9; also elsewhere on the board
GND: J1.6, J1.7, J4.7; also elsewhere on the board
IMU_INT1: J3.6; also elsewhere on the board
IMU_INT2: J4.2; also elsewhere on the board
IOREF: J1.2, TP1.1 (1_1)
LIDAR_INT_3V3: J3.5; also elsewhere on the board
LIDAR_SYNC_3V3: J3.4; also elsewhere on the board
LIDAR_XSHUT_3V3: J4.1; also elsewhere on the board
WIFI_CS: J4.3; also elsewhere on the board
WIFI_EN: J3.8; also elsewhere on the board
WIFI_MISO: J4.5; also elsewhere on the board
WIFI_MOSI: J4.4; also elsewhere on the board
WIFI_RDY: J3.3; also elsewhere on the board
WIFI_SCK: J4.6; also elsewhere on the board

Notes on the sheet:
BARRETTES ARDUINO UNO R3 (males) - la carte s enfiche SOUS le STM32N6570-DK (face opposee a l ecran). Reperes du kit (photos du 03/11/2026, a confirmer) : CN8 alimentation, CN7 A0-A5, CN11 D0-D7, CN12 D8-D15. Broches du N6 d apres le schema MB1939 page 3 : D0 PF6, D1 PD5, D2 PD0, D3 PE9, D4 PH5, D5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
